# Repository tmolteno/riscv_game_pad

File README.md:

# riscv_game_pad
Small game pad project, based on https://github.com/wagiminator/CH32V003-GameConsole/

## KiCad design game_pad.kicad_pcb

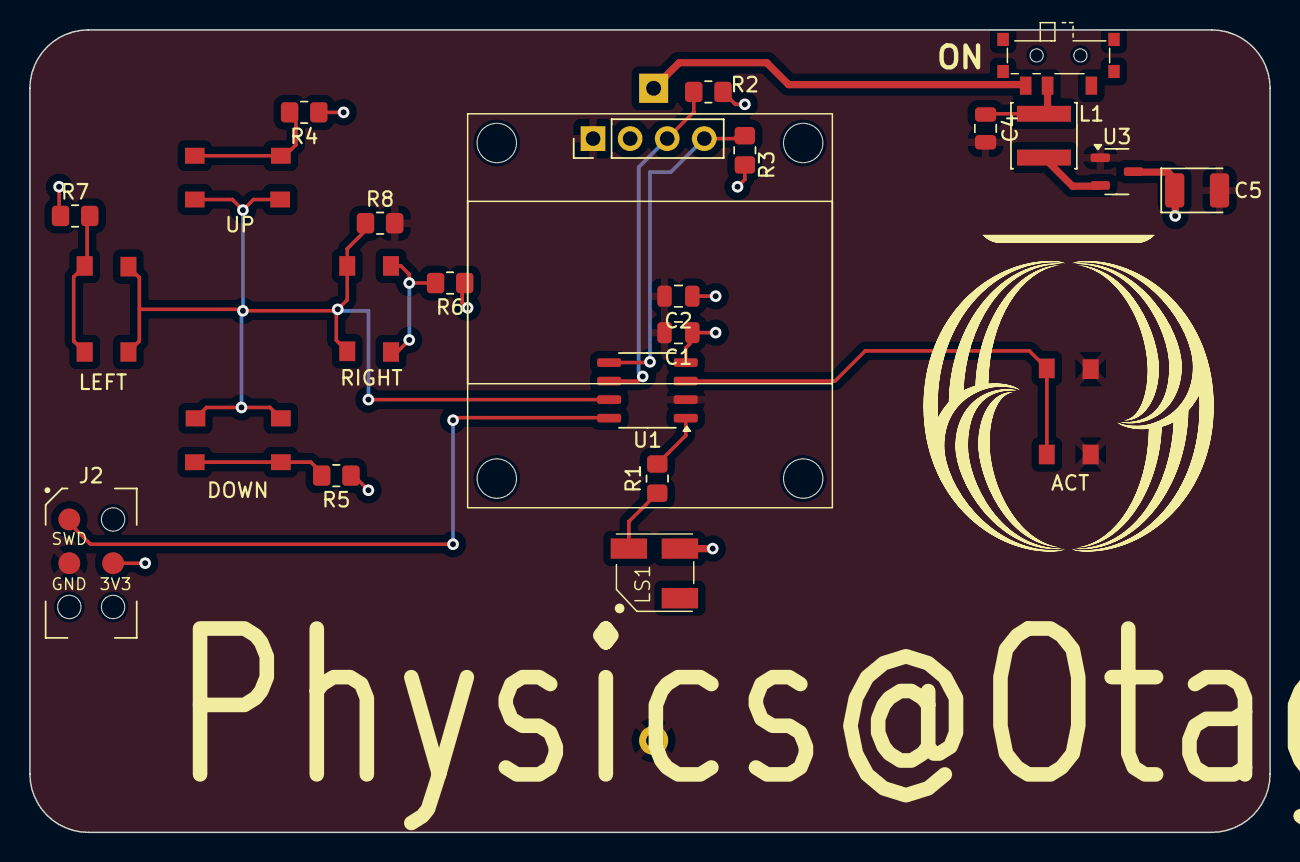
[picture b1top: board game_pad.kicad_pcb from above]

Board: 2 copper layers, 85.0 x 55.0 mm, 25 parts (1 on the bottom side), 16 nets.

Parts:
BT1: AAA; BatteryHolder_Keystone_2466_1xAAA
C1: 100n; C_0805_2012Metric
C2: 10u; C_0805_2012Metric
C4: 10uF; C_0805_2012Metric
C5: 100uF; CP_EIA-3528-21_Kemet-B
J2: swd-connect-3; swd-connect-3-mcu
L1: 22uH; L_Sunlord_SWPA4030S
LS1: Speaker; MLT-5030
R1: 22; R_0805_2012Metric_Pad1.20x1.40mm_HandSolder
R2, R3: 2.2k; R_0805_2012Metric_Pad1.20x1.40mm_HandSolder
R4: 8.2k; R_0805_2012Metric_Pad1.20x1.40mm_HandSolder
R5: 3.9k; R_0805_2012Metric_Pad1.20x1.40mm_HandSolder
R6: 20k; R_0805_2012Metric_Pad1.20x1.40mm_HandSolder
R7, R8: 2k; R_0805_2012Metric_Pad1.20x1.40mm_HandSolder
SW1: TA-3524A-A1
SW2: ACT; TSC015
SW3: UP; TSC015
SW4: DOWN; TSC015
SW5: RIGHT; TSC015
SW6: LEFT; TSC015
U1: CH32v003; SOP-8_3.9x4.9mm_P1.27mm
U2: Screen; OLED_0.96_128x64_I2C_SSD1306
U3: ME2188A33XG; SOT-23-3

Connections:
+BATT: C4.1, L1.1, SW1.2 (C)
ACT: SW2.1, U1.3 (PA2)
BEEP: R1.2, U1.1 (PD6/PA1)
DIO: J2.1 (SWD), U1.8 (PD1/4/5)
GND: BT1.2 (-), C1.2, C2.2, C4.2, C5.2, J2.2 (GND), R8.2, SW2.2, U1.2 (VSS), U2.1 (GND), U3.1 (Vss)
unnamed: BT1.1 (+), SW1.3 (B)
unnamed: LS1.2, R1.1
unnamed: R4.2, SW3.1
unnamed: R5.2, SW4.1
unnamed: R6.2, SW5.1
unnamed: R7.2, SW6.1
unnamed: L1.2, U3.2 (Lx)
OLED_SCL: R2.2, U1.6 (PC2), U2.3 (SCL)
OLED_SDA: R3.2, U1.5 (PC1), U2.4 (SDA)
PAD: R8.1, SW3.2, SW4.2, SW5.2, SW6.2, U1.7 (PC4)
VCC: C1.1, C2.1, C5.1, J2.3 (3V3), LS1.1, R2.1, R3.1, R4.1, R5.1, R6.1, R7.1, U1.4 (VDD), U2.2 (3V3), U3.3 (Vout)
